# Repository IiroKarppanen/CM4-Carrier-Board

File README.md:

# Custom carrier board for Raspberry Compute Module 4

- USB-C port for Infiray P2 pro thermal camera module
- Connector for Raspberry camera module
- GPIO header
- Charging circuit for LiPo/Li-ion battery
- Connectors for Raspberry Compute Module 4

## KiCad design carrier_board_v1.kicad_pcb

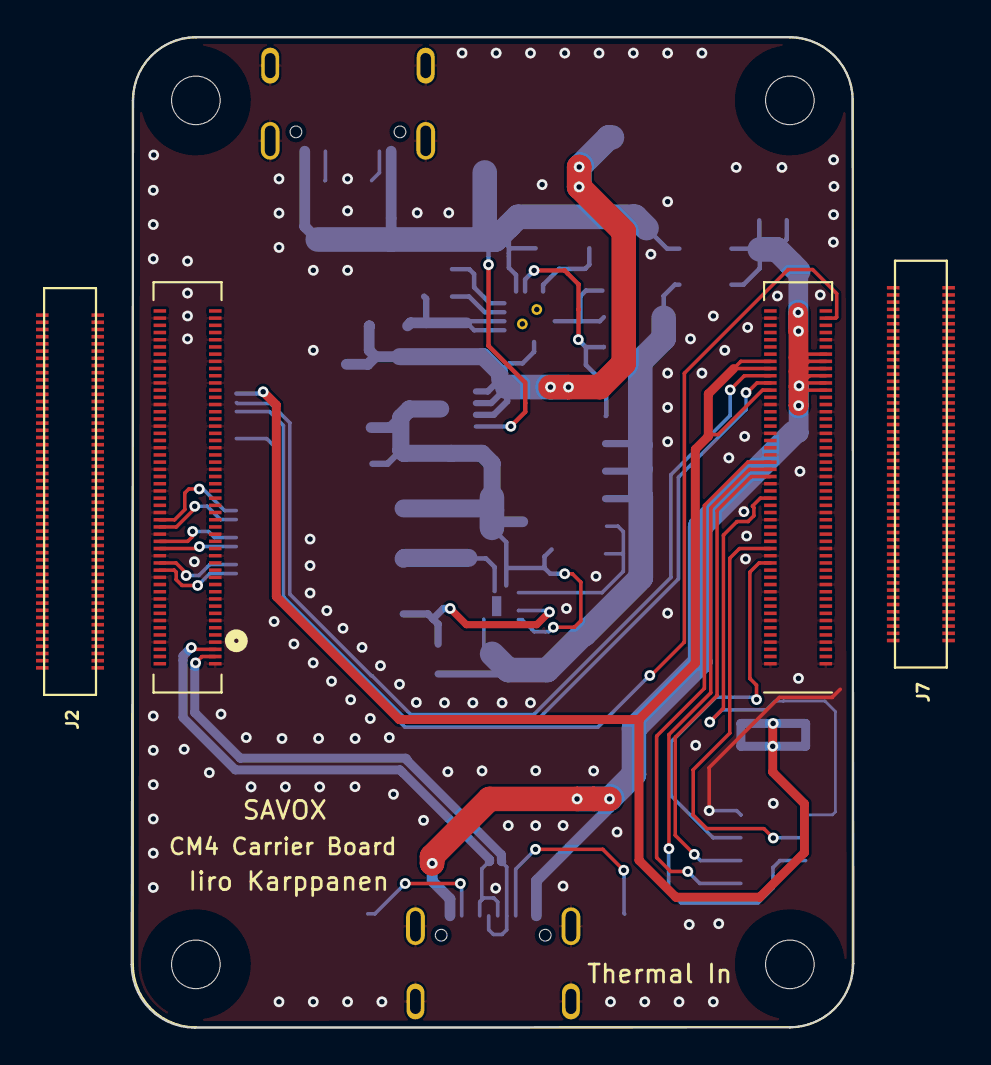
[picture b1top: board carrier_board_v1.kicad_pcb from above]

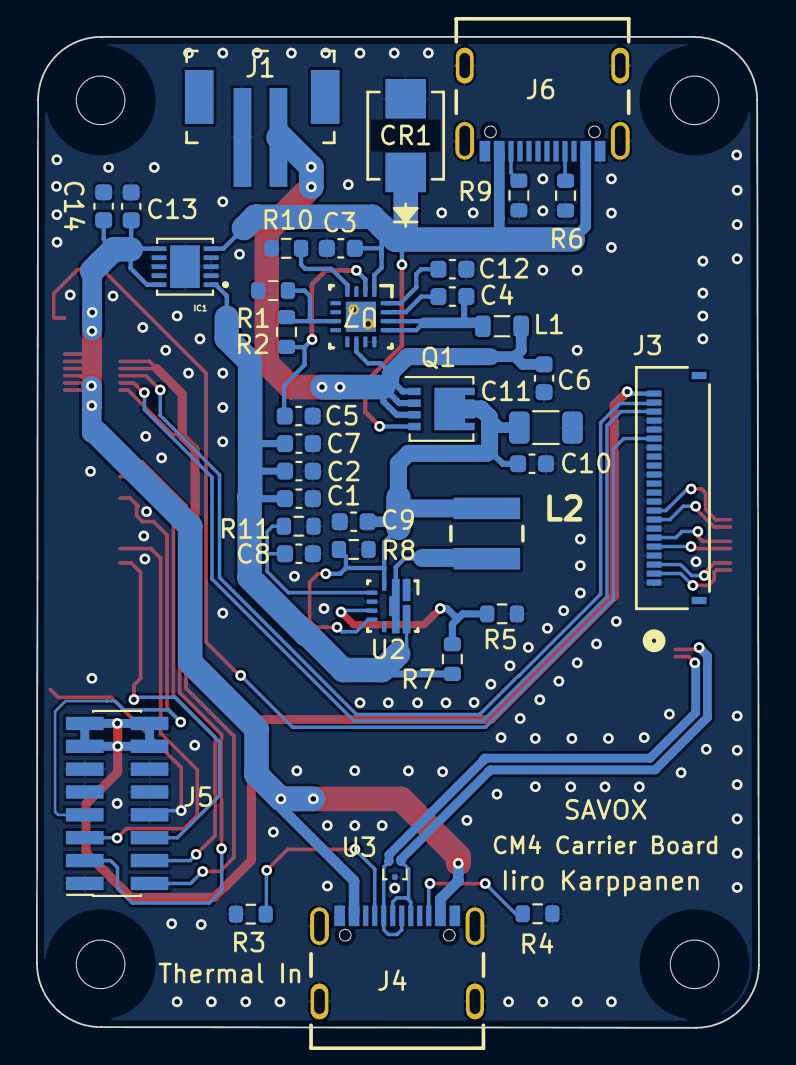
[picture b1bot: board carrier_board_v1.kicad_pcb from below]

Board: 2 copper layers, 40.1 x 55.1 mm, 41 parts (38 on the bottom side), 37 nets.

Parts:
C1, C2, C7: 22uF; C_0603_1608Metric
C3, C5, C12: 2.2uF; C_0603_1608Metric
C4: 47nF; C_0603_1608Metric
C6, C8, C10, C13, C14: 10uF; C_0603_1608Metric
C9: 1uF; C_0603_1608Metric
C11: 47uF; C_1206_3216Metric
CR1: SMBJ5.0A-TR; SMB_STM
IC1: LTC4413EDD-1#PBF; SON50P300X300X80-11N
J1: C157930; PinHeader_1x2_P2mm
J2, J7: DF40C-100DS-0.4V(51); HRS_DF40C-100DS-0.4V(51)
J3: FH34SRJ-22S-0.5SH50; CONN22x1_FH34SRJ-22S-0.5SH50_HIR
J4, J6: C2997432; GCT_USB4105-GF-A
J5: C2938398; PinSocket_2x08_P1.27mm_Vertical_SMD
L1: 1uH; L_0805_2012Metric
L2: MDMK4040T1R0MM
Module1: DF40C-100DS-0.4V(51); Raspberry-Pi-4-Compute-Module
Q1: DMP3013SFV; Diodes_PowerDI3333-8
R1, R2: 10k; R_0603_1608Metric
R3, R4: 5.1k; R_0603_1608Metric
R5: 332k; R_0603_1608Metric
R6, R9: 5.1kΩ; R_0603_1608Metric
R7, R8: 1M; R_0603_1608Metric
R10: 40.2k; R_0603_1608Metric
R11: 61.9k; R_0603_1608Metric
U2: TPS61235PRWLT; RWL0009A
U3: TPD2EUSB30DRTR; Texas_DRT-3
U7: BQ25302RTER; RTE0016C

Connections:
+3.3V: J3.22, J5.13, J5.14, J5.15, J5.16, Module1.78 (GPIO_VREF(1.8v/3.3v_Input)), Module1.84 (+3.3v_(Output)), Module1.86 (+3.3v_(Output))
+5V: C13.1, C14.1, IC1.6 (OUTB), IC1.10 (OUTA), J4.A4_B9 (VBUS), J4.B4_A9 (VBUS), Module1.77 (+5v_(Input)), Module1.79 (+5v_(Input)), Module1.81 (+5v_(Input)), Module1.83 (+5v_(Input)), Module1.85 (+5v_(Input)), Module1.87 (+5v_(Input))
/CM4 Camera pins/CAM0_C_N: J3.8, Module1.140 (CAM0_C_N)
/CM4 Camera pins/CAM0_C_P: J3.9, Module1.142 (CAM0_C_P)
/CM4 Camera pins/CAM0_D0_N: J3.2, Module1.128 (CAM0_D0_N)
/CM4 Camera pins/CAM0_D0_P: J3.3, Module1.130 (CAM0_D0_P)
/CM4 Camera pins/CAM0_D1_N: J3.5, Module1.134 (CAM0_D1_N)
/CM4 Camera pins/CAM0_D1_P: J3.6, Module1.136 (CAM0_D1_P)
/CM4 Camera pins/USB2_N: J4.A7 (DN1), J4.B7 (DN2), Module1.103 (USB2_N), U3.2 (D-)
/CM4 Camera pins/USB2_P: J4.A6 (DP1), J4.B6 (DP2), Module1.105 (USB2_P), U3.1 (D+)
/CM4 GPIO and power pins/GPIO2: J5.2, Module1.58 (GPIO2)
/CM4 GPIO and power pins/GPIO3: J5.3, Module1.56 (GPIO3)
/CM4 GPIO and power pins/GPIO4: J5.4, Module1.54 (GPIO4)
/CM4 GPIO and power pins/GPIO5: J5.5, Module1.34 (GPIO5)
/CM4 GPIO and power pins/GPIO6: J5.6, Module1.30 (GPIO6)
/CM4 GPIO and power pins/GPIO27: J5.7, Module1.48 (GPIO27)
/CM4 GPIO and power pins/REGN: C5.1, R2.1, U7.2 (REGN)
CAM_GPIO: J3.17, Module1.97 (Camera_GPIO)
GND: C1.2, C2.2, C3.2, C5.2, C6.2, C7.2, C8.2, C9.2, C10.2, C11.2, C12.2, C13.2, C14.2, CR1.2, IC1.2 (ENBA), IC1.3 (GND), IC1.4 (ENBB), IC1.11 (SGND), J1.1, J3.1, J3.4, J3.7, J3.10, J3.13, J3.16, J3.18, J3.19, J4.A1_B12 (GND), J4.B1_A12 (GND), J4.S1 (SHELL_GND), J4.S2 (SHELL_GND), J4.S3 (SHELL_GND), J4.S4 (SHELL_GND), J5.1, J5.8, J5.9, J5.10, J5.11, J5.12, J6.A1_B12 (GND), J6.B1_A12 (GND), J6.S1 (SHELL_GND), J6.S2 (SHELL_GND), J6.S3 (SHELL_GND), J6.S4 (SHELL_GND), Module1.1 (GND), Module1.2 (GND), Module1.7 (GND), Module1.8 (GND), Module1.13 (GND), Module1.14 (GND), Module1.22 (GND), Module1.23 (GND), Module1.32 (GND), Module1.33 (GND), Module1.42 (GND), Module1.43 (GND), Module1.52 (GND), Module1.53 (GND), Module1.59 (GND), Module1.60 (GND), Module1.65 (GND), Module1.66 (GND), Module1.71 (GND), Module1.74 (GND), Module1.91 (BT_nDisable), Module1.98 (GND), Module1.101 (USB_OTG_ID), Module1.107 (GND), Module1.108 (GND), Module1.113 (GND), Module1.114 (GND), Module1.119 (GND), Module1.120 (GND), Module1.125 (GND), Module1.126 (GND), Module1.131 (GND), Module1.132 (GND), Module1.137 (GND), Module1.138 (GND), Module1.144 (GND), Module1.150 (GND), Module1.155 (GND), Module1.156 (GND), Module1.161 (GND), Module1.162 (GND), Module1.167 (GND), Module1.168 (GND), Module1.173 (GND), Module1.174 (GND), Module1.179 (GND), Module1.180 (GND), Module1.185 (GND), Module1.186 (GND), Module1.191 (GND), Module1.192 (GND), Module1.197 (GND), Module1.198 (GND), R1.1, R3.1, R4.1, R5.2, R6.1, R8.2, R9.1, R10.2, R11.2, U2.1 (PGND), U2.5 (AGND), U3.3 (GND), U7.11 (GND), U7.12 (GND)
unnamed: C4.1, L1.2, U7.13 (SW), U7.14 (SW)
unnamed: C1.1, C2.1, C7.1, IC1.1 (INA), R7.1, U2.9 (VOUT)
unnamed: C3.1, CR1.1, IC1.5 (INB), J6.A4_B9 (VBUS), J6.B4_A9 (VBUS), Q1.4 (G), U7.1 (VBUS)
unnamed: J4.A5 (CC1), R3.2
unnamed: J4.B5 (CC2), R4.2
unnamed: J6.A5 (CC1), R6.2
unnamed: J6.B5 (CC2), R9.2
unnamed: C9.1, C10.1, C11.1, L2.2, Q1.5 (D), R8.1, U2.3 (VIN), U2.7 (EN)
unnamed: C8.1, R11.1, U2.4 (CC)
unnamed: R5.1, R7.2, U2.6 (FB)
unnamed: L2.1, U2.2 (SW)
unnamed: C6.1, J1.2, L1.1, Q1.1 (S), Q1.2 (S), Q1.3 (S), U7.10 (BAT)
unnamed: C4.2, U7.15 (BTST)
unnamed: R10.1, U7.4 (ICHG)
unnamed: C12.1, U7.16 (PMID)
unnamed: R1.2, R2.2, U7.7 (TS)
SCL0: J3.20, Module1.80 (SCL0)
SDA0: J3.21, Module1.82 (SDA0)

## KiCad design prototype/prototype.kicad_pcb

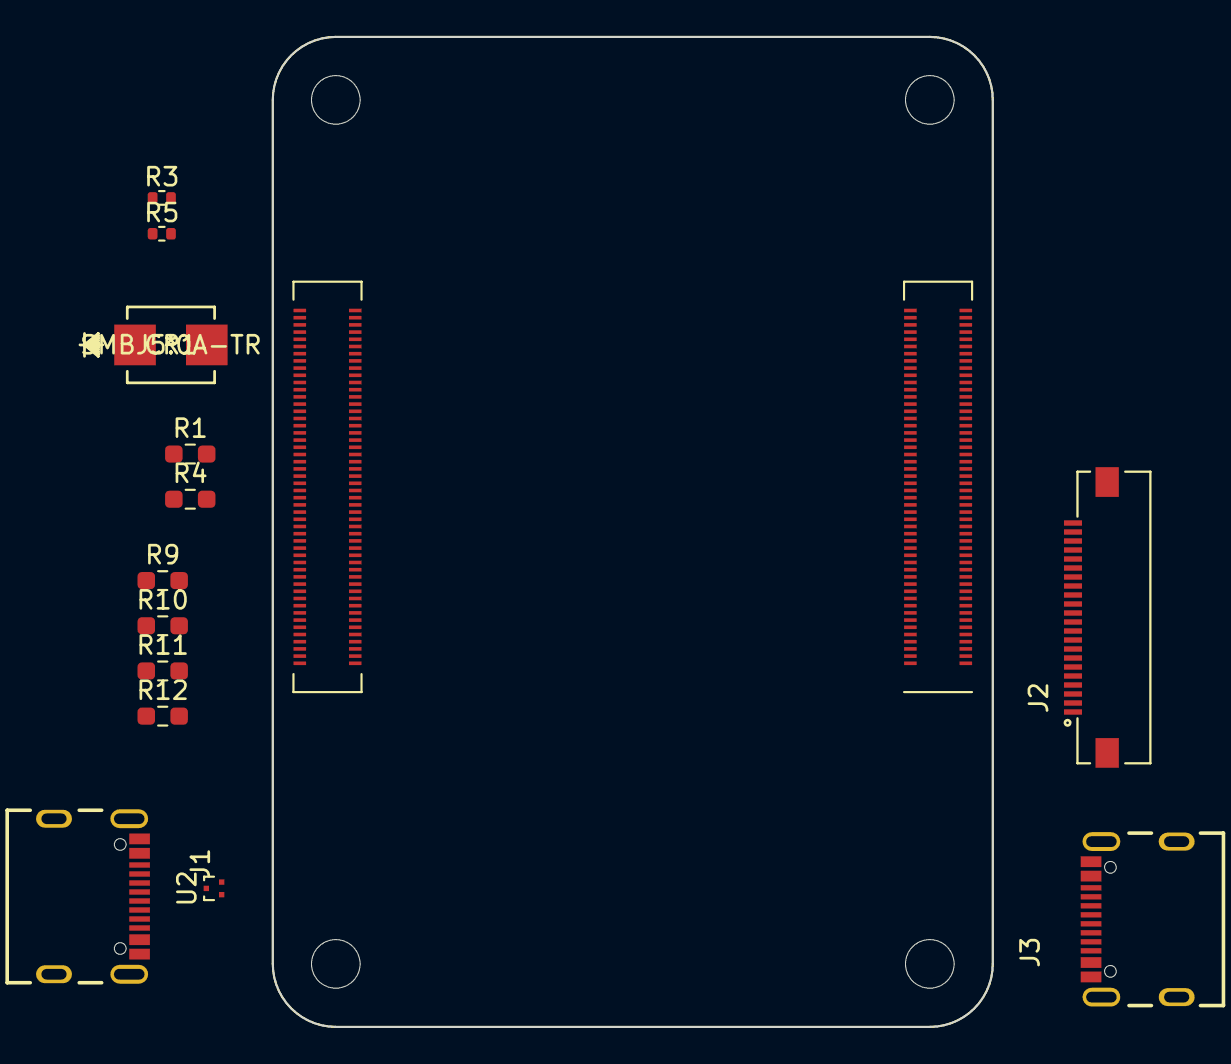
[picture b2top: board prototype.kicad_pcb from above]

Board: 2 copper layers, 40.0 x 55.0 mm, 14 parts (0 on the bottom side), 15 nets, no tracks yet.

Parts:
CR1: SMBJ5.0A-TR
J1, J3: USB4105-GF-A; GCT_USB4105-GF-A
J2: 54548-2271; MOLEX_54548-2271
Module1: ComputeModule4-CM4; Raspberry-Pi-4-Compute-Module
R1, R4, R9, R10: 5.1k; R_0603_1608Metric_Pad0.98x0.95mm_HandSolder
R3, R5: 2.2K 1%; R_0402_1005Metric
R11, R12: 2.2K 1%; R_0603_1608Metric_Pad0.98x0.95mm_HandSolder
U2: TPD2EUSB30; Texas_DRT-3

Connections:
+1.8V: Module1.88 (+1.8v_(Output)), Module1.90 (+1.8v_(Output))
+3.3V: J2.22, Module1.84 (+3.3v_(Output)), Module1.86 (+3.3v_(Output))
+5V: CR1.1, J3.A4_B9 (VBUS), J3.B4_A9 (VBUS), Module1.77 (+5v_(Input)), Module1.79 (+5v_(Input)), Module1.81 (+5v_(Input)), Module1.83 (+5v_(Input)), Module1.85 (+5v_(Input)), Module1.87 (+5v_(Input))
/CM4 High Speed/CAM0_D0_P: J2.3, Module1.130 (CAM0_D0_P)
/CM4 High Speed/CAM0_D1_P: J2.6, Module1.136 (CAM0_D1_P)
/CM4 High Speed/GPIO_VREF: R3.1, R5.1
/CM4 High Speed/SCL1: J2.20, J2.21, R3.2, R5.2
/CM4 High Speed/USB2_N: J1.A6 (DP1), J1.A7 (DN1), J1.B6 (DP2), J1.B7 (DN2), Module1.101 (USB_OTG_ID), Module1.103 (USB2_N), Module1.105 (USB2_P), R11.2, R12.1, U2.1 (D+), U2.2 (D-)
GND: CR1.2, J1.A1_B12 (GND), J1.B1_A12 (GND), J2.1, J2.2, J2.4, J2.5, J2.7, J2.8, J2.9, J2.10, J2.13, J2.16, J2.19, J3.A1_B12 (GND), J3.B1_A12 (GND), J3.S1 (SHELL_GND), J3.S2 (SHELL_GND), J3.S3 (SHELL_GND), J3.S4 (SHELL_GND), Module1.1 (GND), Module1.2 (GND), Module1.7 (GND), Module1.8 (GND), Module1.13 (GND), Module1.14 (GND), Module1.22 (GND), Module1.23 (GND), Module1.32 (GND), Module1.33 (GND), Module1.42 (GND), Module1.43 (GND), Module1.52 (GND), Module1.53 (GND), Module1.59 (GND), Module1.60 (GND), Module1.65 (GND), Module1.66 (GND), Module1.71 (GND), Module1.74 (GND), Module1.98 (GND), Module1.107 (GND), Module1.108 (GND), Module1.113 (GND), Module1.114 (GND), Module1.119 (GND), Module1.120 (GND), Module1.125 (GND), Module1.126 (GND), Module1.128 (CAM0_D0_N), Module1.131 (GND), Module1.132 (GND), Module1.134 (CAM0_D1_N), Module1.137 (GND), Module1.138 (GND), Module1.140 (CAM0_C_N), Module1.142 (CAM0_C_P), Module1.144 (GND), Module1.150 (GND), Module1.155 (GND), Module1.156 (GND), Module1.161 (GND), Module1.162 (GND), Module1.167 (GND), Module1.168 (GND), Module1.173 (GND), Module1.174 (GND), Module1.179 (GND), Module1.180 (GND), Module1.185 (GND), Module1.186 (GND), Module1.191 (GND), Module1.192 (GND), Module1.197 (GND), Module1.198 (GND), R1.2, R4.2, R9.2, R10.2, R12.2, U2.3 (GND)
unnamed: J1.A5 (CC1), R9.1
unnamed: J1.B5 (CC2), R10.1
unnamed: J1.S1 (SHELL_GND), J1.S2 (SHELL_GND), J1.S3 (SHELL_GND), J1.S4 (SHELL_GND)
unnamed: J1.A4_B9 (VBUS), J1.B4_A9 (VBUS), R11.1
unnamed: J3.A5 (CC1), R1.1
unnamed: J3.B5 (CC2), R4.1

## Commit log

2023-06-21 updated library paths
2023-06-27 uorked on lipo charging circuit
2023-06-28 schematic almost ready
2023-07-03 schematic complete
2023-07-04 pää hajoo
2023-07-04 send help
2023-07-06 what the fuck
2023-07-06 almost ready
2023-07-16 final commit
2023-07-17 version 2
2023-07-18 almost
2023-07-19 complete
2023-08-11 version3 complete

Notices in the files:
carrier_board_v1.kicad_pcb:
creativecommons.org/licenses/by/4.0
License: CC BY 4.0
parts and their libraries:
Copyright 2016 Accelerated Designs. All rights reserved.
